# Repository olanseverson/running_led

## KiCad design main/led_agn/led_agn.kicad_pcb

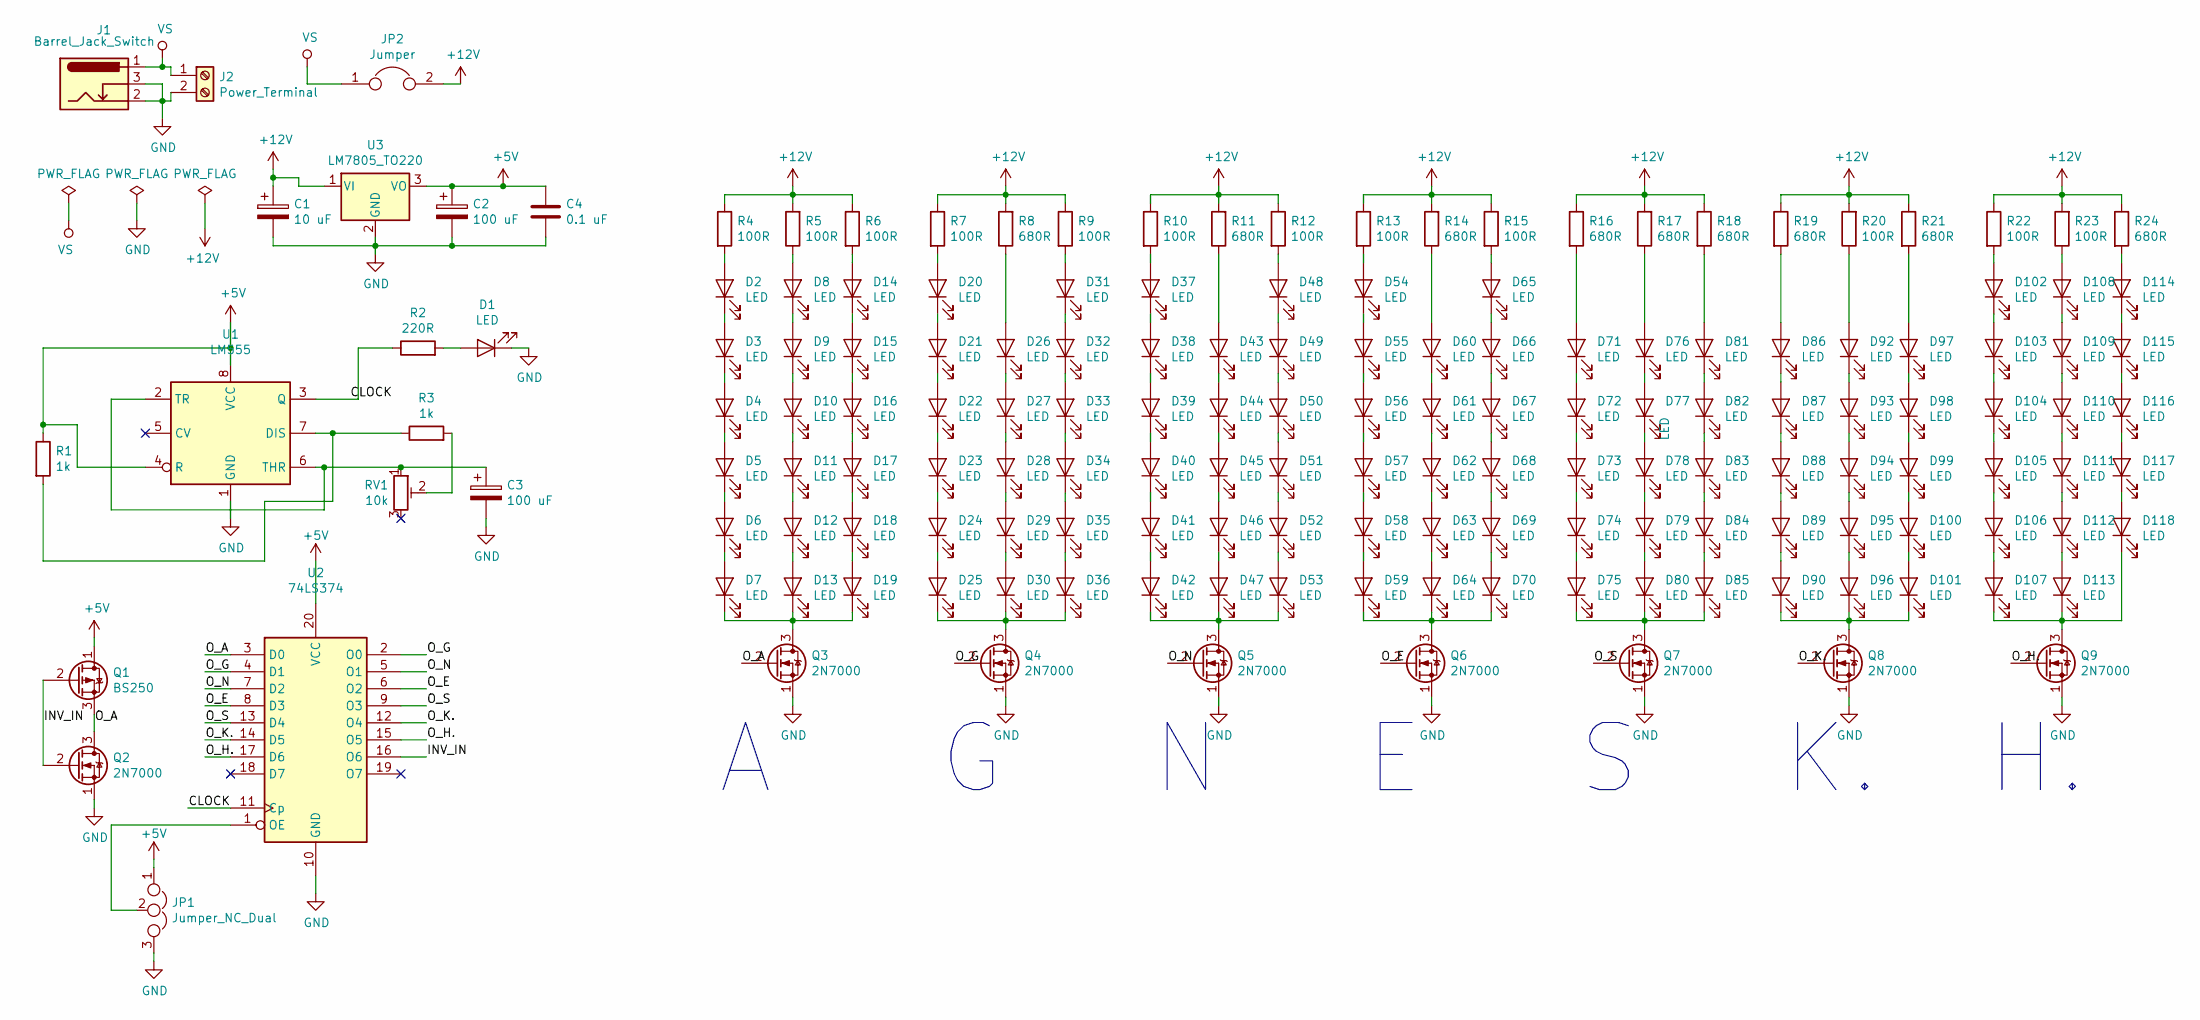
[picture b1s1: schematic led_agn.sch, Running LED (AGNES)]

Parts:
C1: 10 uF; CP_Radial_D5.0mm_P2.50mm
C2, C3: 100 uF; CP_Radial_D5.0mm_P2.50mm
C4: 0.1 uF; C_Disc_D12.0mm_W4.4mm_P7.75mm
D1, D2, D3, D4, D5, D6, D7, D8, D9, D10, D11, D12, D13, D14, D15, D16, D17, D18, D19, D20, D21, D22, D23, D24, D25, D26, D27, D28, D29, D30, D31, D32, D33, D34, D35, D36, D37, D38, D39, D40, D41, D42, D43, D44, D45, D46, D47, D48, D49, D50, D51, D52, D53, D54, D55, D56, D57, D58, D59, D60, D61, D62, D63, D64, D65, D66, D67, D68, D69, D70, D71, D72, D73, D74, D75, D76, D77, D78, D79, D80, D81, D82, D83, D84, D85, D86, D87, D88, D89, D90, D92, D93, D94, D95, D96, D97, D98, D99, D100, D101, D102, D103, D104, D105, D106, D107, D108, D109, D110, D111, D112, D113, D114, D115, D116, D117, D118: LED; LED_D3.0mm
J1: Barrel_Jack_Switch; BarrelJack_Wuerth_6941xx301002
J2: Power_Terminal; TerminalBlock_bornier-2_P5.08mm
JP1: Jumper_NC_Dual; PinHeader_1x03_P2.54mm_Vertical
JP2: Jumper; PinHeader_1x02_P2.54mm_Vertical
Q1: BS250; TO-92_Inline_Wide
Q2, Q3, Q4, Q5, Q6, Q7, Q8, Q9: 2N7000; TO-92_Inline_Wide
R1, R3: 1k; R_Axial_DIN0207_L6.3mm_D2.5mm_P10.16mm_Horizontal
R2: 220R; R_Axial_DIN0207_L6.3mm_D2.5mm_P10.16mm_Horizontal
R4, R5, R6, R7, R9, R10, R12, R13, R15, R20, R22, R23: 100R; R_Axial_DIN0207_L6.3mm_D2.5mm_P10.16mm_Horizontal
R8, R11, R14, R16, R17, R18, R19, R21, R24: 680R; R_Axial_DIN0207_L6.3mm_D2.5mm_P10.16mm_Horizontal
RV1: 10k; Potentiometer_Bourns_3386X_Horizontal
U1: LM555; DIP-8_W7.62mm_Socket
U2: 74LS374; DIP-20_W7.62mm_Socket_LongPads
U3: LM7805_TO220; TO-220-3_Vertical

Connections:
+5V: C2.1, C4.1, JP1.1, Q1.1 (D), R1.1, U1.4 (R), U1.8 (VCC), U2.20 (VCC), U3.3 (VO)
+12V: C1.1, JP2.2, R4.1, R5.2, R6.1, R7.1, R8.2, R9.1, R10.1, R11.2, R12.1, R13.1, R14.2, R15.1, R16.1, R17.2, R18.1, R19.1, R20.2, R21.1, R22.1, R23.2, R24.1, U3.1 (VI)
/CLOCK: R2.1, U1.3 (Q), U2.11 (Cp)
/INV_IN: Q1.2 (G), Q2.2 (G), U2.16 (O6)
/O_A: Q1.3 (S), Q2.3 (D), Q3.2 (G), U2.3 (D0)
/O_E: Q6.2 (G), U2.6 (O2), U2.8 (D3)
/O_G: Q4.2 (G), U2.2 (O0), U2.4 (D1)
/O_H.: Q9.2 (G), U2.15 (O5), U2.17 (D6)
/O_K.: Q8.2 (G), U2.12 (O4), U2.14 (D5)
/O_N: Q5.2 (G), U2.5 (O1), U2.7 (D2)
/O_S: Q7.2 (G), U2.9 (O3), U2.13 (D4)
GND: C1.2, C2.2, C3.2, C4.2, D1.1 (K), J1.2, J1.3, J2.2, JP1.3, Q2.1 (S), Q3.1 (S), Q4.1 (S), Q5.1 (S), Q6.1 (S), Q7.1 (S), Q8.1 (S), Q9.1 (S), U1.1 (GND), U2.10 (GND), U3.2 (GND)
unnamed: C3.1, RV1.1, U1.2 (TR), U1.6 (THR)
unnamed: D1.2 (A), R2.2
unnamed: D2.1 (K), D3.2 (A)
unnamed: D2.2 (A), R4.2
unnamed: D3.1 (K), D4.2 (A)
unnamed: D4.1 (K), D5.2 (A)
unnamed: D5.1 (K), D6.2 (A)
unnamed: D6.1 (K), D7.2 (A)
unnamed: D8.1 (K), D9.2 (A)
unnamed: D8.2 (A), R5.1
unnamed: D10.1 (K), D11.2 (A)
unnamed: D9.1 (K), D10.2 (A)
unnamed: D11.1 (K), D12.2 (A)
unnamed: D12.1 (K), D13.2 (A)
unnamed: D7.1 (K), D13.1 (K), D19.1 (K), Q3.3 (D)
unnamed: D14.1 (K), D15.2 (A)
unnamed: D14.2 (A), R6.2
unnamed: D15.1 (K), D16.2 (A)
unnamed: D16.1 (K), D17.2 (A)
unnamed: D17.1 (K), D18.2 (A)
unnamed: D18.1 (K), D19.2 (A)
unnamed: D20.1 (K), D21.2 (A)
unnamed: D20.2 (A), R7.2
unnamed: D21.1 (K), D22.2 (A)
unnamed: D22.1 (K), D23.2 (A)
unnamed: D23.1 (K), D24.2 (A)
unnamed: D24.1 (K), D25.2 (A)
unnamed: D25.1 (K), D30.1 (K), D36.1 (K), Q4.3 (D)
unnamed: D26.1 (K), D27.2 (A)
unnamed: D26.2 (A), R8.1
unnamed: D27.1 (K), D28.2 (A)
unnamed: D28.1 (K), D29.2 (A)
unnamed: D29.1 (K), D30.2 (A)
unnamed: D31.1 (K), D32.2 (A)
unnamed: D31.2 (A), R9.2
unnamed: D32.1 (K), D33.2 (A)
unnamed: D33.1 (K), D34.2 (A)
unnamed: D34.1 (K), D35.2 (A)
unnamed: D35.1 (K), D36.2 (A)
unnamed: D37.1 (K), D38.2 (A)
unnamed: D37.2 (A), R10.2
unnamed: D38.1 (K), D39.2 (A)
unnamed: D39.1 (K), D40.2 (A)
unnamed: D40.1 (K), D41.2 (A)
unnamed: D41.1 (K), D42.2 (A)
unnamed: D42.1 (K), D47.1 (K), D53.1 (K), Q5.3 (D)
unnamed: D43.1 (K), D44.2 (A)
unnamed: D43.2 (A), R11.1
unnamed: D44.1 (K), D45.2 (A)
unnamed: D45.1 (K), D46.2 (A)
unnamed: D46.1 (K), D47.2 (A)
unnamed: D48.1 (K), D49.2 (A)
unnamed: D48.2 (A), R12.2
unnamed: D49.1 (K), D50.2 (A)
unnamed: D50.1 (K), D51.2 (A)
unnamed: D51.1 (K), D52.2 (A)
unnamed: D52.1 (K), D53.2 (A)
unnamed: D54.1 (K), D55.2 (A)
unnamed: D54.2 (A), R13.2
unnamed: D55.1 (K), D56.2 (A)
unnamed: D56.1 (K), D57.2 (A)
unnamed: D57.1 (K), D58.2 (A)
unnamed: D58.1 (K), D59.2 (A)
unnamed: D59.1 (K), D64.1 (K), D70.1 (K), Q6.3 (D)
unnamed: D60.1 (K), D61.2 (A)
unnamed: D60.2 (A), R14.1
unnamed: D61.1 (K), D62.2 (A)
unnamed: D62.1 (K), D63.2 (A)
unnamed: D63.1 (K), D64.2 (A)
unnamed: D65.1 (K), D66.2 (A)
unnamed: D65.2 (A), R15.2
unnamed: D66.1 (K), D67.2 (A)
unnamed: D67.1 (K), D68.2 (A)
unnamed: D68.1 (K), D69.2 (A)
unnamed: D69.1 (K), D70.2 (A)
unnamed: D71.1 (K), D72.2 (A)
unnamed: D71.2 (A), R16.2
unnamed: D72.1 (K), D73.2 (A)
unnamed: D73.1 (K), D74.2 (A)
unnamed: D74.1 (K), D75.2 (A)
unnamed: D75.1 (K), D80.1 (K), D85.1 (K), Q7.3 (D)
unnamed: D76.1 (K), D77.2 (A)
unnamed: D76.2 (A), R17.1
unnamed: D77.1 (K), D78.2 (A)
unnamed: D78.1 (K), D79.2 (A)
unnamed: D79.1 (K), D80.2 (A)
unnamed: D81.1 (K), D82.2 (A)
unnamed: D81.2 (A), R18.2
unnamed: D82.1 (K), D83.2 (A)
unnamed: D83.1 (K), D84.2 (A)
unnamed: D84.1 (K), D85.2 (A)
unnamed: D86.1 (K), D87.2 (A)
unnamed: D86.2 (A), R19.2
unnamed: D87.1 (K), D88.2 (A)
unnamed: D88.1 (K), D89.2 (A)
unnamed: D89.1 (K), D90.2 (A)
unnamed: D92.1 (K), D93.2 (A)
unnamed: D92.2 (A), R20.1
unnamed: D93.1 (K), D94.2 (A)
unnamed: D94.1 (K), D95.2 (A)
unnamed: D95.1 (K), D96.2 (A)
unnamed: D97.1 (K), D98.2 (A)
unnamed: D97.2 (A), R21.2
unnamed: D98.1 (K), D99.2 (A)
unnamed: D100.1 (K), D101.2 (A)
unnamed: D99.1 (K), D100.2 (A)
unnamed: D90.1 (K), D96.1 (K), D101.1 (K), Q8.3 (D)
unnamed: D102.1 (K), D103.2 (A)
unnamed: D102.2 (A), R22.2
unnamed: D103.1 (K), D104.2 (A)
unnamed: D104.1 (K), D105.2 (A)
unnamed: D105.1 (K), D106.2 (A)
unnamed: D106.1 (K), D107.2 (A)
unnamed: D107.1 (K), D113.1 (K), D118.1 (K), Q9.3 (D)
unnamed: D108.1 (K), D109.2 (A)
unnamed: D108.2 (A), R23.1
unnamed: D109.1 (K), D110.2 (A)
unnamed: D110.1 (K), D111.2 (A)
unnamed: D111.1 (K), D112.2 (A)
unnamed: D112.1 (K), D113.2 (A)
unnamed: D114.1 (K), D115.2 (A)
unnamed: D114.2 (A), R24.2
unnamed: D115.1 (K), D116.2 (A)
unnamed: D116.1 (K), D117.2 (A)
unnamed: D117.1 (K), D118.2 (A)
unnamed: JP1.2, U2.1 (OE)
unnamed: R1.2, R3.1, U1.7 (DIS)
unnamed: R3.2, RV1.2
VS: J1.1, J2.1, JP2.1

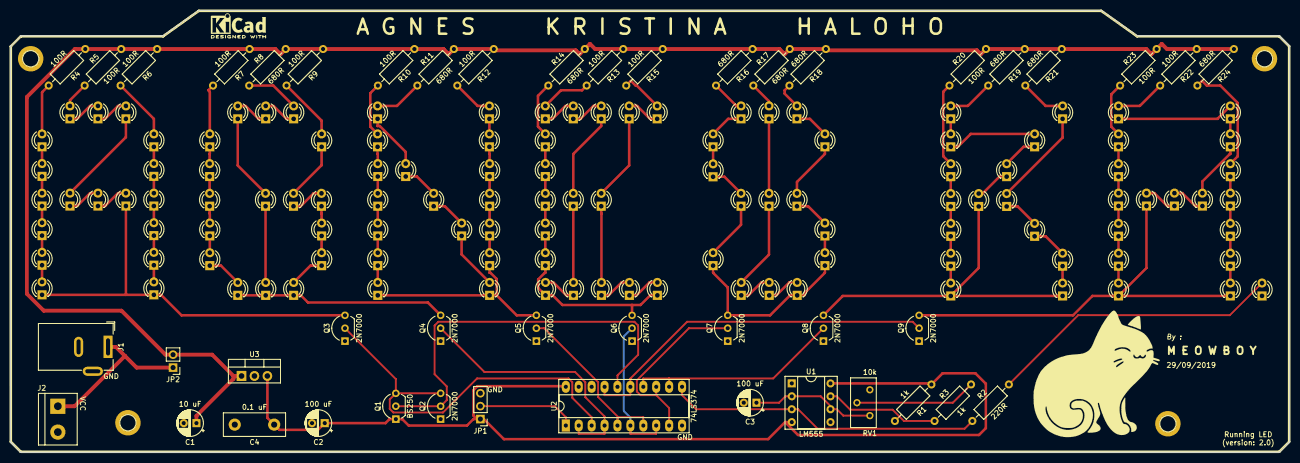
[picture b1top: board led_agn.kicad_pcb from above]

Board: 2 copper layers, 251.6 x 86.9 mm, 162 parts (0 on the bottom side), 141 nets.

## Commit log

2019-08-25 before adding header jumper
2019-08-25 sebelum sampai ke percetakan
2019-08-28 Change track width
2019-09-07 typo
2019-09-14 add new project led agn
2019-09-14 edit resistor
2019-09-23 forming main text
2019-09-28 add already-placed design (before routing)
2019-09-29 after autoroute (before adding logo)
2019-09-29 adding watermark, gerber file
2019-10-01 before sending to manufacturer
